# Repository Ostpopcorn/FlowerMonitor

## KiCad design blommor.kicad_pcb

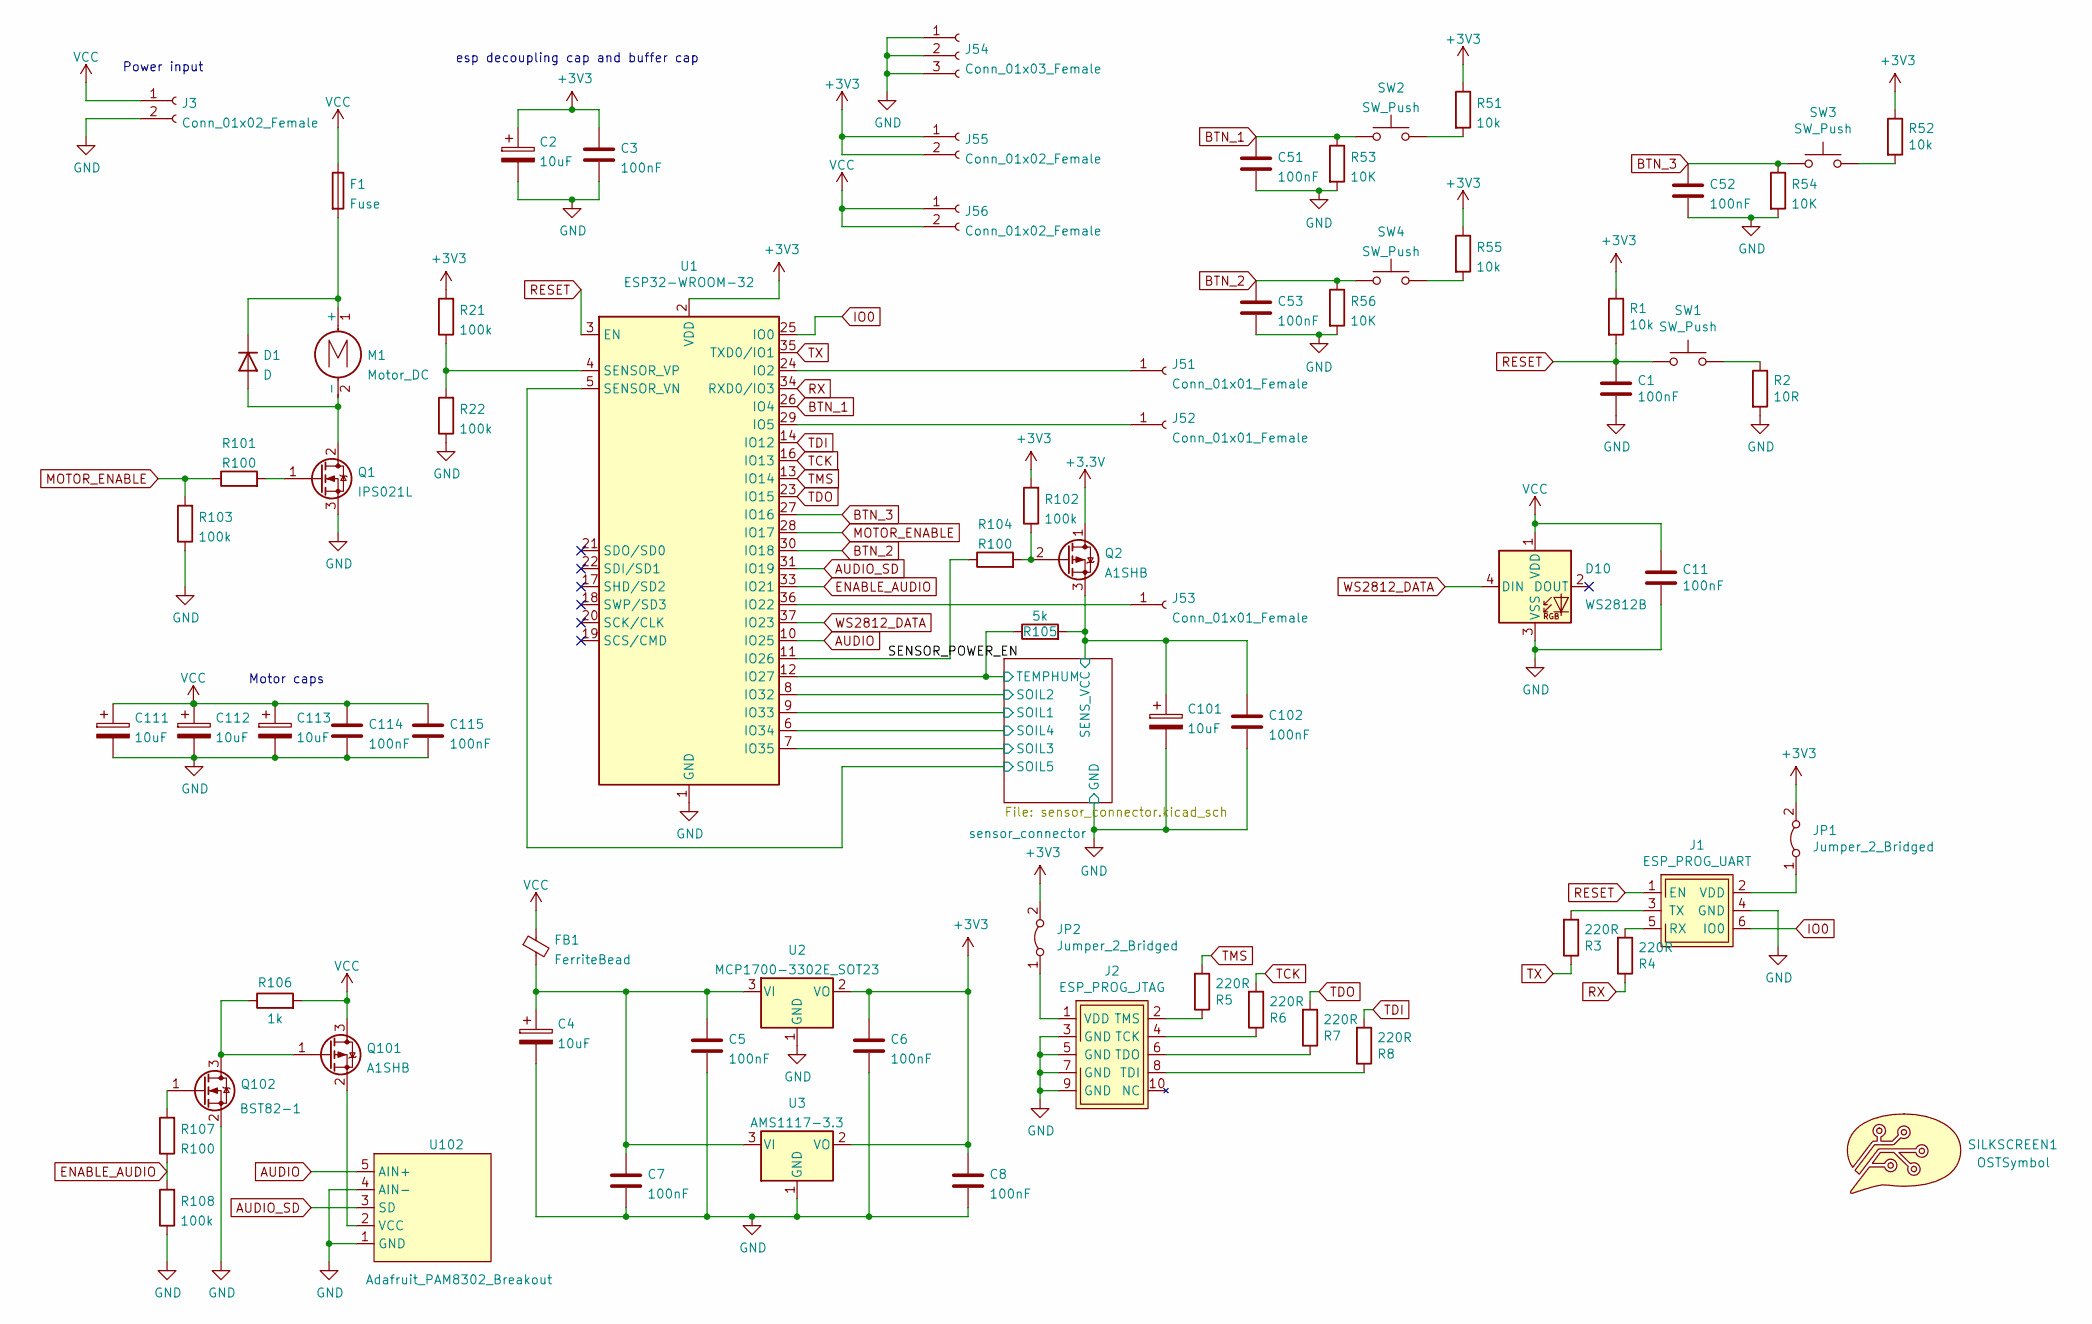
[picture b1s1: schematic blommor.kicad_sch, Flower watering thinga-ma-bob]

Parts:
C1, C3, C5, C6, C7, C8, C11, C51, C52, C53, C102, C114, C115: 100nF; C_0603_1608Metric_Pad1.08x0.95mm_HandSolder
C2, C4, C101, C111, C112, C113: 10uF; CP_Elec_10x10.5
D1: D; D_DO-15_P15.24mm_Horizontal
D10: WS2812B; LED_WS2812B_PLCC4_5.0x5.0mm_P3.2mm
F1: Fuse; Fuseholder_Cylinder-5x20mm_Stelvio-Kontek_PTF78_Horizontal_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
FB1: FerriteBead; R_1206_3216Metric_Pad1.30x1.75mm_HandSolder
J1: ESP_PROG_UART; SMT_ESP_PROG_PROG_1.27
J2: ESP_PROG_JTAG; SMT_ESP_PROG_JTAG_1.27
J3: Conn_01x02_Female; JST_PH_B2B-PH-SM4-TB_1x02-1MP_P2.00mm_Vertical
J51, J52, J53: Conn_01x01_Female; PinSocket_1x01_P2.54mm_Vertical
J54: Conn_01x03_Female; PinSocket_1x03_P2.54mm_Vertical
J55, J56: Conn_01x02_Female; PinSocket_1x02_P2.54mm_Vertical
JP1, JP2: Jumper_2_Bridged; SolderJumper-2_P1.3mm_Open_TrianglePad1.0x1.5mm
M1: Motor_DC; JST_XH_B2B-XH-A_1x02_P2.50mm_Vertical
Q1: IPS021L; SOT-223-3_TabPin2
Q2, Q101: A1SHB; SOT-23
Q102: BST82-1; SOT-23
R1, R51, R52, R55: 10k; R_0603_1608Metric_Pad0.98x0.95mm_HandSolder
R2: 10R; R_0603_1608Metric_Pad0.98x0.95mm_HandSolder
R3, R4, R5, R6, R7, R8: 220R; R_0603_1608Metric_Pad0.98x0.95mm_HandSolder
R21, R22, R102, R103, R108: 100k; R_0603_1608Metric_Pad0.98x0.95mm_HandSolder
R53, R54, R56: 10K; R_0603_1608Metric_Pad0.98x0.95mm_HandSolder
R101, R104, R107: R100; R_0603_1608Metric_Pad0.98x0.95mm_HandSolder
R105: 5k; R_0603_1608Metric_Pad0.98x0.95mm_HandSolder
R106: 1k; R_0603_1608Metric_Pad0.98x0.95mm_HandSolder
SILKSCREEN1: OSTSymbol; ost-bubble_12mm_SilkScreen
SW1: SW_Push; SW_SPST_TL3342
SW2, SW3, SW4: SW_Push; SW_PUSH_6mm_H5mm
U1: ESP32-WROOM-32
U2: MCP1700-3302E_SOT23; SOT-23
U3: AMS1117-3.3; SOT-223-3_TabPin2
U102: Adafruit_PAM8302_Breakout

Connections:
/SENSOR_POWER_EN: R104.1, U1.11 (IO26)
/sensor_connector/SENS_VCC: C101.1, C102.1, Q2.3 (S), R105.2; also elsewhere on the board
/sensor_connector/SOIL1: U1.9 (IO33); also elsewhere on the board
/sensor_connector/SOIL2: U1.8 (IO32); also elsewhere on the board
/sensor_connector/SOIL3: U1.7 (IO35); also elsewhere on the board
/sensor_connector/SOIL4: U1.6 (IO34); also elsewhere on the board
/sensor_connector/SOIL5: U1.5 (SENSOR_VN); also elsewhere on the board
/sensor_connector/TEMPHUM: R105.1, U1.12 (IO27); also elsewhere on the board
AUDIO: U1.10 (IO25), U102.5 (AIN+)
AUDIO_SD: U1.31 (IO19), U102.3 (SD)
BTN_1: C51.1, R53.1, SW2.1, U1.26 (IO4)
BTN_2: C53.1, R56.1, SW4.1, U1.30 (IO18)
BTN_3: C52.1, R54.1, SW3.1, U1.27 (IO16)
ENABLE_AUDIO: R107.1, R108.2, U1.33 (IO21)
GND: C1.2, C2.2, C3.2, C4.2, C5.2, C6.2, C7.2, C8.2, C11.2, C51.2, C52.2, C53.2, C101.2, C102.2, C111.2, C112.2, C113.2, C114.2, C115.2, D10.3 (VSS), J1.4 (GND), J2.3 (GND), J2.5 (GND), J2.7 (GND), J2.9 (GND), J3.2, J54.1, J54.2, J54.3, Q1.3 (S), Q102.2 (S), R2.2, R22.1, R53.2, R54.2, R56.2, R103.1, R108.1, U1.1 (GND), U1.15 (GND), U1.38 (GND), U1.39 (GND), U2.1 (GND), U3.1 (GND), U102.1 (GND), U102.4 (AIN-); also elsewhere on the board
IO0: J1.6 (IO0), U1.25 (IO0)
MOTOR_ENABLE: R101.1, R103.2, U1.28 (IO17)
unnamed: C4.1, C5.1, C7.1, FB1.2, U2.3 (VI), U3.3 (VI)
unnamed: D1.1 (K), F1.2, M1.1 (+)
unnamed: D1.2 (A), M1.2 (-), Q1.2 (D)
unnamed: J1.2 (VDD), JP1.1 (A)
unnamed: J1.3 (TX), R3.2
unnamed: J1.5 (RX), R4.2
unnamed: J2.1 (VDD), JP2.1 (A)
unnamed: J2.2 (TMS), R5.1
unnamed: J2.4 (TCK), R6.1
unnamed: J2.6 (TDO), R7.1
unnamed: J2.8 (TDI), R8.1
unnamed: J51.1, U1.24 (IO2)
unnamed: J52.1, U1.29 (IO5)
unnamed: J53.1, U1.36 (IO22)
unnamed: Q1.1 (G), R101.2
unnamed: Q2.2 (G), R102.1, R104.2
unnamed: Q101.1 (G), Q102.3 (D), R106.1
unnamed: Q101.2 (S), U102.2 (VCC)
unnamed: Q102.1 (G), R107.2
unnamed: R2.1, SW1.2
unnamed: R21.1, R22.2, U1.4 (SENSOR_VP)
unnamed: R51.2, SW2.2
unnamed: R52.2, SW3.2
unnamed: R55.2, SW4.2
RESET: C1.1, J1.1 (EN), R1.2, SW1.1, U1.3 (EN)
RX: R4.1, U1.34 (RXD0/IO3)
TCK: R6.2, U1.16 (IO13)
TDI: R8.2, U1.14 (IO12)
TDO: R7.2, U1.23 (IO15)
TMS: R5.2, U1.13 (IO14)
TX: R3.1, U1.35 (TXD0/IO1)
VCC: C11.1, C111.1, C112.1, C113.1, C114.1, C115.1, D10.1 (VDD), F1.1, FB1.1, J3.1, J56.1, J56.2, Q101.3 (D), R106.2
WS2812_DATA: D10.4 (DIN), U1.37 (IO23)

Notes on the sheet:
esp decoupling cap and buffer cap
Motor caps
Power input

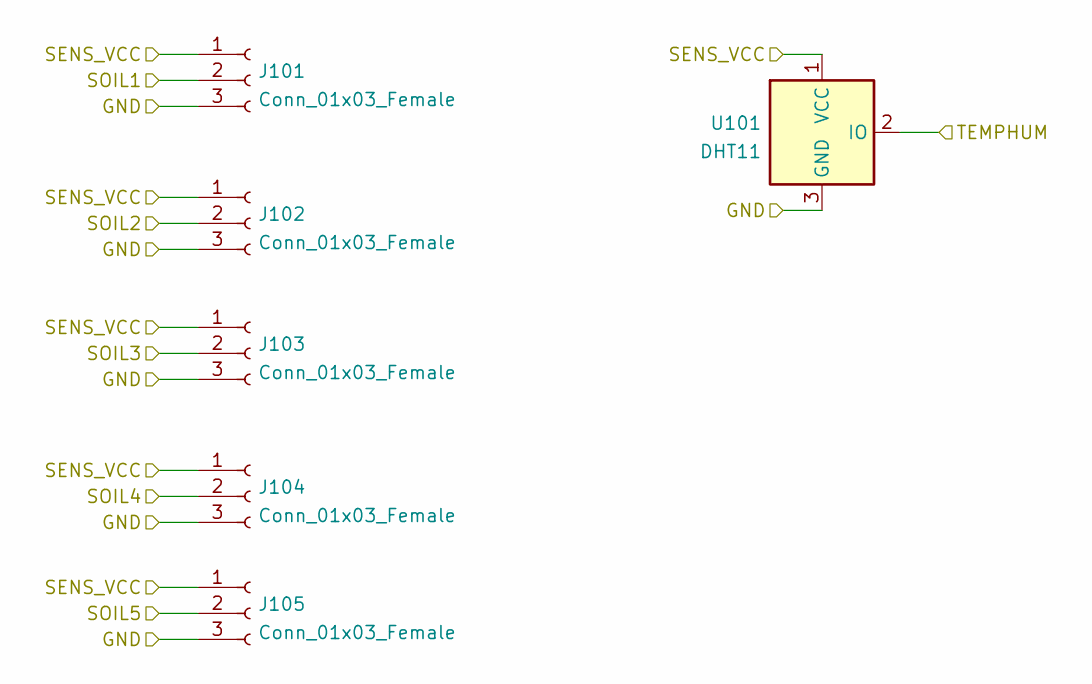
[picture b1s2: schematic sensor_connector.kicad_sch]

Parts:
J101, J102, J103, J104, J105: Conn_01x03_Female; JST_XH_B3B-XH-A_1x03_P2.50mm_Vertical
U101: DHT11; PinSocket_1x03_P2.54mm_Vertical

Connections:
/sensor_connector/SENS_VCC: J101.1, J102.1, J103.1, J104.1, J105.1, U101.1 (VCC); also elsewhere on the board
/sensor_connector/SOIL1: J101.2; also elsewhere on the board
/sensor_connector/SOIL2: J102.2; also elsewhere on the board
/sensor_connector/SOIL3: J103.2; also elsewhere on the board
/sensor_connector/SOIL4: J104.2; also elsewhere on the board
/sensor_connector/SOIL5: J105.2; also elsewhere on the board
/sensor_connector/TEMPHUM: U101.2 (IO); also elsewhere on the board
GND: J101.3, J102.3, J103.3, J104.3, J105.3, U101.3 (GND); also elsewhere on the board

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
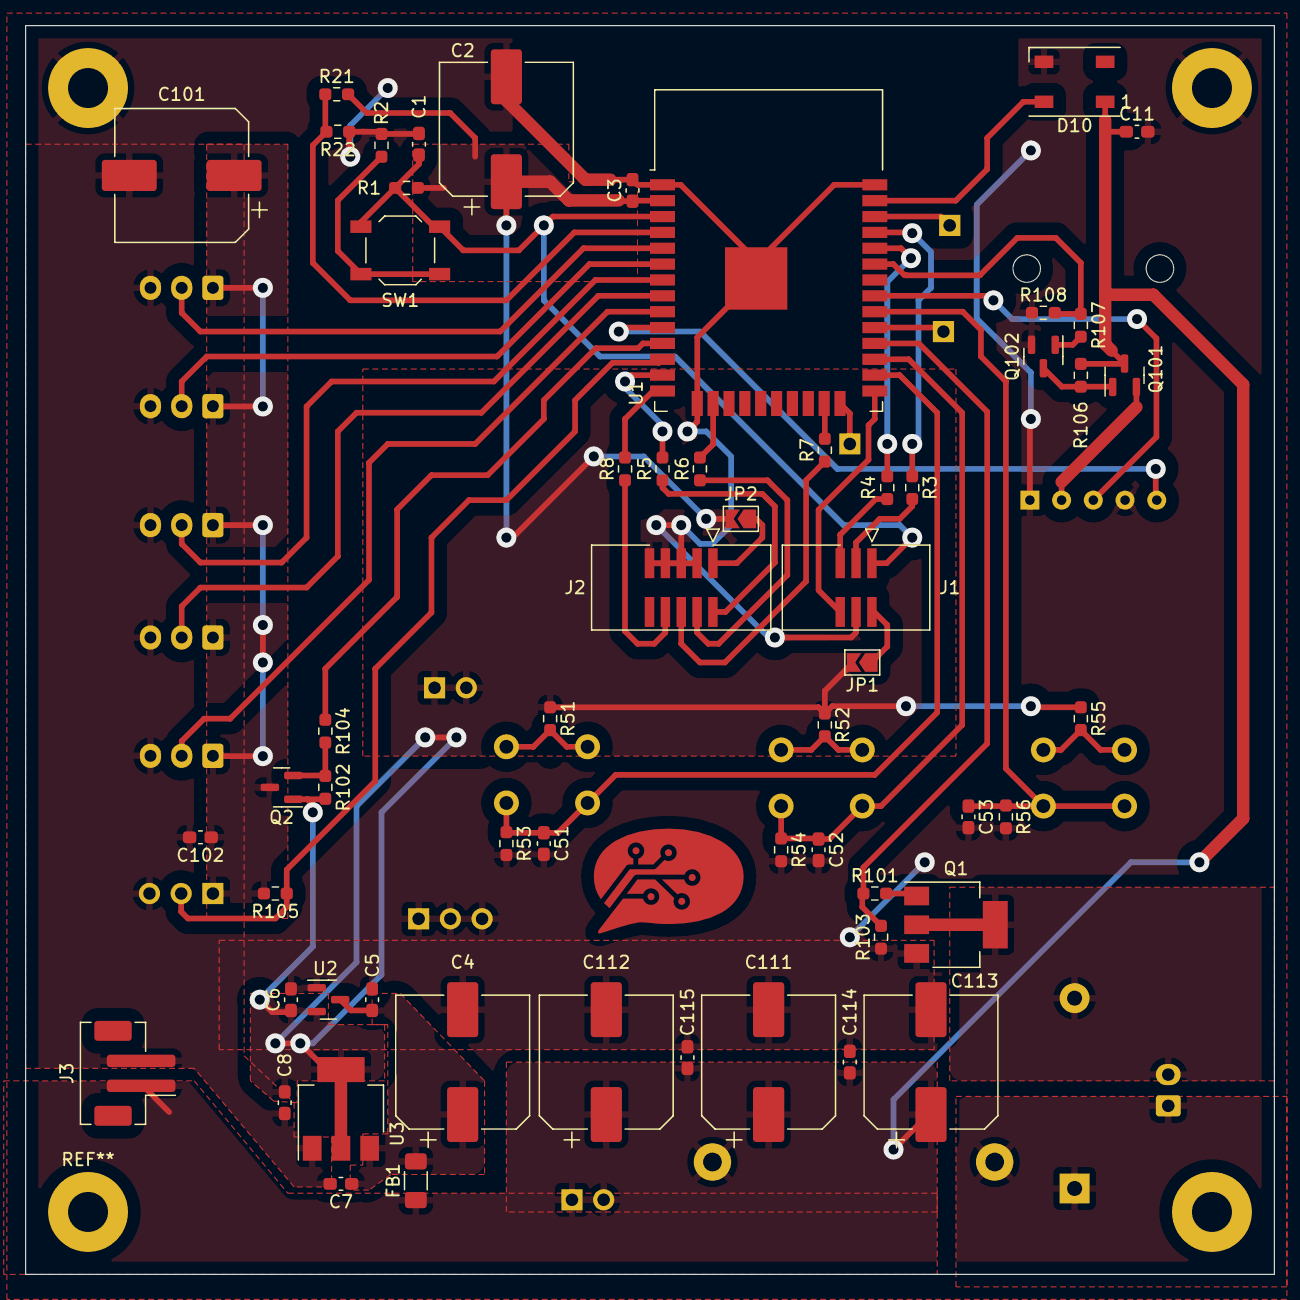
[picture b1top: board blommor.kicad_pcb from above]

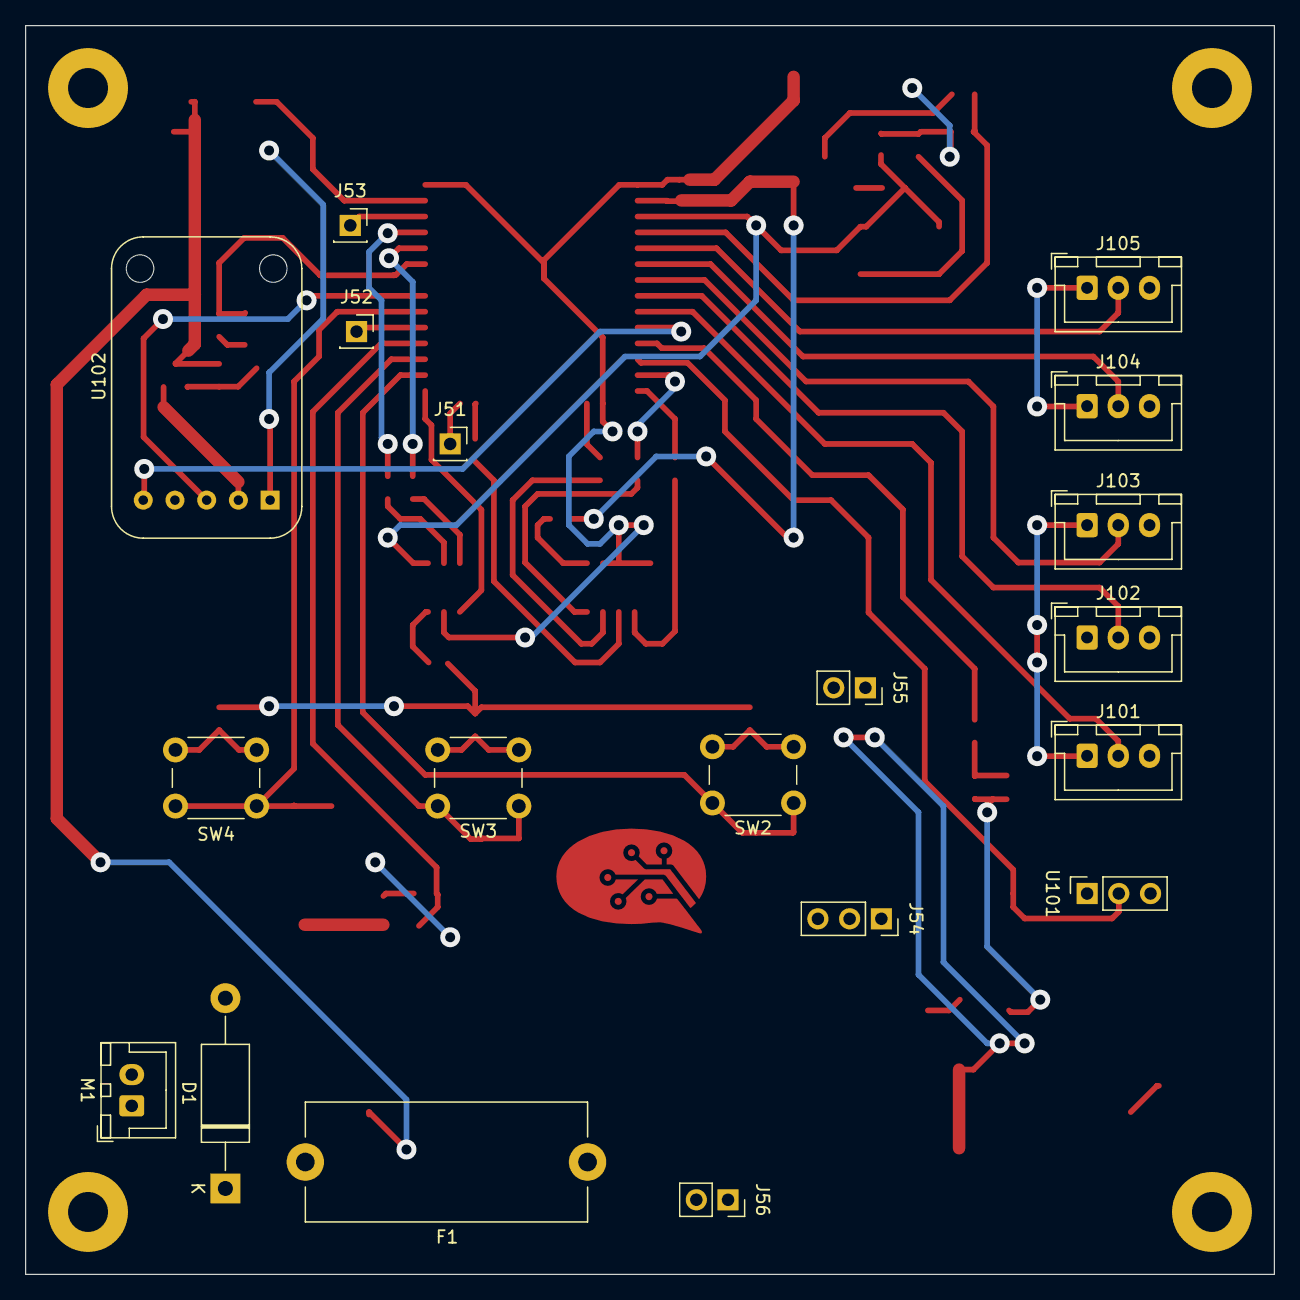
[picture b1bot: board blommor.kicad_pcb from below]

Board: 2 copper layers, 100.0 x 100.0 mm, 79 parts (20 on the bottom side), 51 nets.

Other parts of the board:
ost-bubble_12mm_Copper: G***; ost-bubble_12mm_Copper

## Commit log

2022-02-03 First commit. Many components place in schematic.
2022-02-04 Added Amplifier board om "special" lib. Added Amplifier to board with shutdown pins. Added DHT11 sensor to sensor schematic. Updated connector lib.
2022-02-06 Corrected RESET curcit to not keep the device in reset state. Added more capacitors to be a buffer for the motor. Added fuse to motor.
2022-02-08 Added pcb, not routed but sorted. Gave all footprints refernces. Missing some footprints or might be wrong.
2022-02-08 Added OST logo.
2022-02-08 Forgot to save...
2022-02-08 Renamed ConnectorEsp folder so 3D models work. Started routing and more layout work.
2022-02-10 Typ klar nu.
2022-02-13 Saker saker saker.... PALLA
